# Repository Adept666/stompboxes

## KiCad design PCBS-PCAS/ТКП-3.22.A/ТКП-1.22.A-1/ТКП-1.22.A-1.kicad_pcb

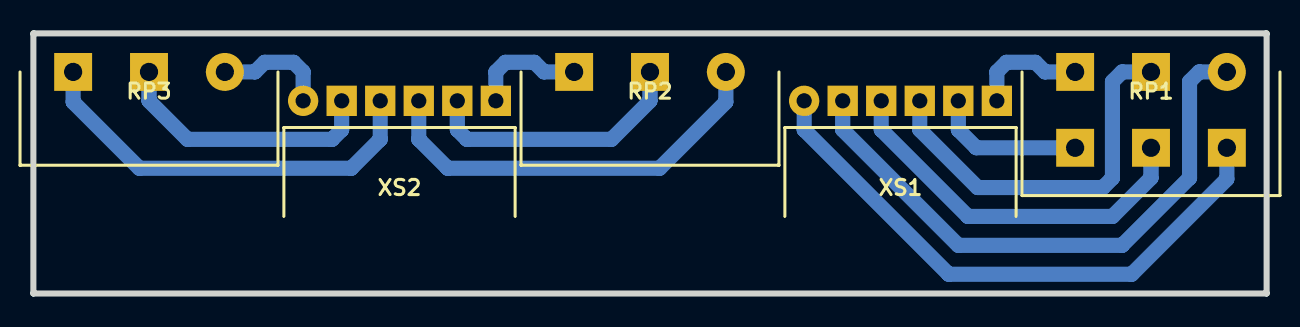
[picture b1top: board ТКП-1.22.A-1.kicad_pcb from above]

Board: 2 copper layers, 81.3 x 17.1 mm, 5 parts (0 on the bottom side), 12 nets.

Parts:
RP1: RP1: B100K; RP-PDB182-K-20-P
RP2: RP2: B10K; RP-PDB181-K-20-P
RP3: RP3: B10K; RP-PDB181-K-20-P
XS1, XS2: PBS-06R; CON-PBS-06R

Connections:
unnamed: RP1.1, XS1.2
unnamed: RP1.2, XS1.4
unnamed: RP1.3, XS1.6
unnamed: RP1.4, XS1.1
unnamed: RP1.5, XS1.3
unnamed: RP1.6, XS1.5
unnamed: RP2.1, XS2.4
unnamed: RP2.2, XS2.5
unnamed: RP2.3, XS2.6
unnamed: RP3.1, XS2.1
unnamed: RP3.2, XS2.2
unnamed: RP3.3, XS2.3

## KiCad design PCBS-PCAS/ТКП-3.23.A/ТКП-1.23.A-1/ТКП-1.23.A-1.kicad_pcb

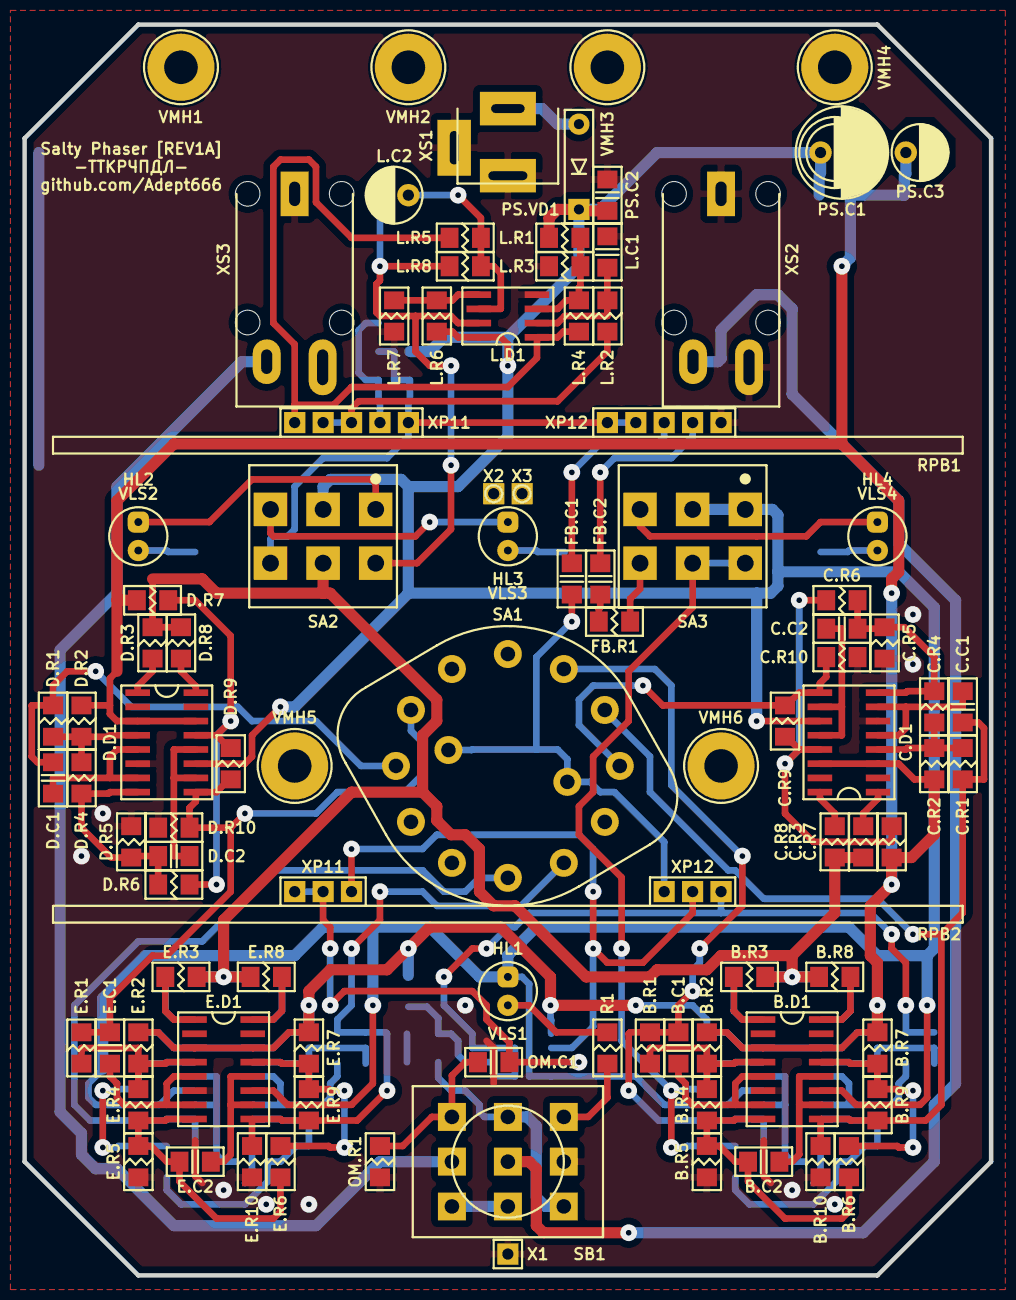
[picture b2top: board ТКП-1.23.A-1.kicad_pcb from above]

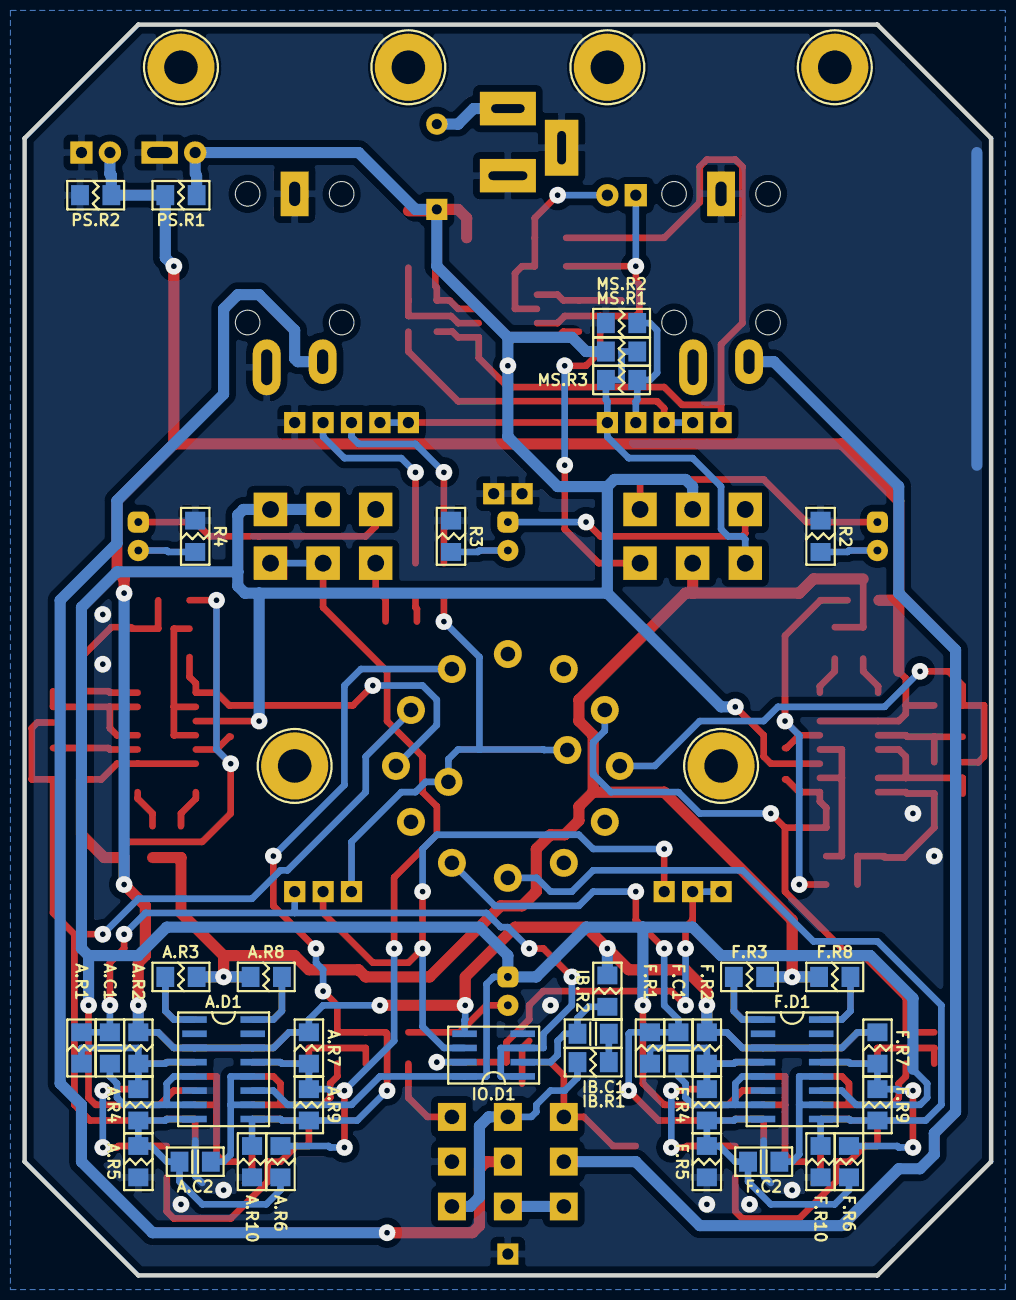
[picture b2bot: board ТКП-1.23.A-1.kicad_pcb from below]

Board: 2 copper layers, 86.4 x 111.8 mm, 160 parts (50 on the bottom side), 85 nets.

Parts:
*R1, *R2: 473; R-SM-0805
*R3: 2612; R-SM-0805
A.C1, A.C2: X; C-SM-1206
A.D1: X; P-SO-16
A.R1, A.R2, A.R3, A.R4, A.R5, A.R6, A.R7, A.R8, A.R9, A.R10: X; R-SM-1206
B.C1, B.C2: X; C-SM-1206
B.D1: X; P-SO-16
B.R1, B.R2, B.R3, B.R4, B.R5, B.R6, B.R7, B.R8, B.R9, B.R10: X; R-SM-1206
C.C1, C.C2: 332; C-SM-1206
C.D1: 13700; P-SO-16
C.R1, C.R4, C.R6, C.R9: 273; R-SM-1206
C.R2, C.R7: 182; R-SM-1206
C.R3, C.R5, C.R8, C.R10: 103; R-SM-1206
D.C1, D.C2: 332; C-SM-1206
D.D1: 13700; P-SO-16
D.R1, D.R4, D.R6, D.R9: 273; R-SM-1206
D.R2, D.R7: 182; R-SM-1206
D.R3, D.R5, D.R8, D.R10: 103; R-SM-1206
E.C1, E.C2: X; C-SM-1206
E.D1: X; P-SO-16
E.R1, E.R2, E.R3, E.R4, E.R5, E.R6, E.R7, E.R8, E.R9, E.R10: X; R-SM-1206
F.C1, F.C2: X; C-SM-1206
F.D1: X; P-SO-16
F.R1, F.R2, F.R3, F.R4, F.R5, F.R6, F.R7, F.R8, F.R9, F.R10: X; R-SM-1206
FB.C1, FB.C2: X; C-SM-1206
FB.R1: X; R-SM-1206
HL1: FYL-5013UWC; LED-ROUND-05.0-UNI-SH-SPACER-PNL-5.3
HL2, HL3, HL4: X; LED-ROUND-05.0-UNI-SH-SPACER-PNL-5.3
IB.C1: 472; C-SM-1206
IB.R1: 103; R-SM-1206
IB.R2: 105; R-SM-1206
IO.D1: 4558; P-SO-08
L.C1: 474; C-SM-1206
L.C2: 475; CP-RADIAL-D05.0-P02.0-CLS
L.D1: 4558; P-SO-08
L.R1, L.R3, L.R4: 364; R-SM-1206
L.R2: 154; R-SM-1206
L.R5, L.R6, L.R8: 103; R-SM-1206
L.R7: 622; R-SM-1206
MS.R1: 331; R-SM-1206
MS.R2: 680; R-SM-1206
MS.R3: 470; R-SM-1206
OM.C1: 473; C-SM-1206
OM.R1: X; R-SM-1206
PS.C1: 107; CP-RADIAL-D05.0-P02.0-CLS-OR-D06.3-P02.5-CLS-OR-D08.0-P03.5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
PS.C2: 104; C-SM-1206
PS.C3: 106; CP-RADIAL-D05.0-P02.0-CLS
PS.R1, PS.R2: 103; R-SM-1206
PS.VD1: 5817; P-DO-41
R1: 103; R-SM-1206
R2, R3, R4: X; R-SM-1206
RPB1: B500K-A1K-B100K; RPB-1590BB-18-3x17-1.5-PNL-7.4-2.8
RPB2: X; RPB-1590BB-18-2x17-1.5-PNL-7.4-2.8
SA1: X; SW-RBS-1-2P6W-VP-PNL-9.5
SA2: MTS-202-A2; SW-MTS-202-A2-3.0-PNL-6.0
SA3: X; SW-MTS-202-A2-3.0-PNL-6.0
SB1: PBS-24-302SP; SW-PBS-24-302SP-2.5-PNL-13.0
VE1: 1590BB; 1590BB_B1
VE2: ТКП-6.1.4.A1.A1.2-1.A1; ТКП-6.1.4.A1.A1
VJ1.1, VJ1.2, VJ3.1, VJ3.2, VJ3.3, VJ3.4: BOTTOM; VJ
VJ2.1, VJ2.2, VJ6.1, VJ6.2, VJ7.1, VJ7.2, VJ8.1, VJ8.2: TOP; VJ
VLS1: BR-12.7; VLS-BR
VLS2, VLS3, VLS4: X; VLS-BR
VMH1, VMH2, VMH3, VMH4, VMH5, VMH6: DI5M3x18; VMH-STA-DA5-PNL-3.0
VTC1, VTC2, VTC3: BOTTOM; VTC
VTC4: TOP; VTC
X1, X2: COM; CON-PAD-S-1.0-1.9
X3: X; CON-PAD-S-1.0-1.9
XS1: DC-005; CON-DC-005
XS2, XS3: ST-008S-05; CON-ST-008X-04-OR-ST-008X-05

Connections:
/DRY: A.C1.1, A.R1.1, IO.D1.1, IO.D1.3, RPB2.31, VJ1.1.1, VJ3.1.1, VJ3.4.1, VTC1.1, VTC3.1
/FB: A.D1.13, A.R6.2, A.R7.1, A.R9.1, SA3.COM2, SA3.NC2
/FB-ON: FB.R1.2, SA3.NO2
/IN-CIR: IB.R1.1, SB1.NC3, SB1.NO2
/IN-CON: SB1.COM2, XS2.T
/LED: R1.1, SB1.NO3
/LED-FB: HL4.A, SA3.NO1
/LED-MS: HL3.A, SA2.NO1
/LED-SPEED: HL2.A, SA2.NC1
/LFO: A.R3.1, A.R8.1, B.R3.1, B.R8.1, C.R3.1, C.R8.1, D.R3.1, D.R8.1, E.R3.1, E.R8.1, F.R3.1, F.R8.1, SA2.COM2
/LFO-AUTO: L.C2.-, L.D1.7, L.R8.2, SA2.NC2
/LFO-MANUAL: MS.R1.1, MS.R3.2, RPB1.22, RPB1.23, SA2.NO2
/OUT2: A.D1.9, A.R9.2, A.R10.1, B.C1.1, B.R1.1, SA1.1-1
/OUT4: B.D1.9, B.R9.2, B.R10.1, C.C1.1, C.R1.1, SA1.1-2, VJ3.3.1
/OUT6: C.D1.9, C.R9.2, C.R10.1, D.C1.1, D.R1.1, SA1.1-3, SA1.2-3, VJ6.1.1, VJ6.2.1
/OUT8: D.D1.9, D.R9.2, D.R10.1, E.C1.1, E.R1.1, SA1.2-4, VJ2.2.1
/OUT10: E.D1.9, E.R9.2, E.R10.1, F.C1.1, F.R1.1, SA1.1-5
/OUT12: F.D1.9, F.R9.2, F.R10.1, SA1.1-6
/OUT-CIR: OM.C1.2, OM.R1.2, SB1.NO1, VJ7.2.1, VJ8.2.1, VTC4.1
/OUT-CON: SB1.COM1, XS3.T
/WET: FB.C1.1, RPB2.33, SA1.COM1, SA1.COM2, VJ2.1.1
COM: A.D1.6, A.R5.2, A.R10.2, B.D1.6, B.R5.2, B.R10.2, C.D1.6, C.R5.2, C.R10.2, D.D1.6, D.R5.2, D.R10.2, E.D1.6, E.R5.2, E.R10.2, F.D1.6, F.R5.2, F.R10.2, IO.D1.4, L.C1.1, L.D1.4, L.R3.1, L.R7.1, MS.R2.1, OM.R1.1, PS.C1.-, PS.C2.2, PS.C3.-, PS.R2.1, R2.1, R3.1, R4.1, RPB1.31, SB1.COM3, VMH1.0, VMH2.0, VMH3.0, VMH4.0, X1.1, X2.1, X3.1, XS1.C, XS1.SN, XS2.R/TN, XS2.S, XS3.S
unnamed: A.C1.2, A.D1.5, A.D1.7
unnamed: A.C2.1, A.D1.8, A.R4.2, A.R5.1, A.R6.1
unnamed: A.C2.2, A.D1.10, A.D1.12
unnamed: A.D1.1, A.R3.2
unnamed: A.D1.4, A.R1.2, A.R2.1, A.R4.1
unnamed: A.D1.16, A.R8.2
unnamed: B.C1.2, B.D1.5, B.D1.7
unnamed: B.C2.1, B.D1.8, B.R4.2, B.R5.1, B.R6.1
unnamed: B.C2.2, B.D1.10, B.D1.12
unnamed: B.D1.1, B.R3.2
unnamed: B.D1.4, B.R1.2, B.R2.1, B.R4.1
unnamed: B.D1.13, B.R6.2, B.R7.1, B.R9.1
unnamed: B.D1.16, B.R8.2
unnamed: C.C1.2, C.D1.5, C.D1.7
unnamed: C.C2.1, C.D1.8, C.R4.2, C.R5.1, C.R6.1
unnamed: C.C2.2, C.D1.10, C.D1.12
unnamed: C.D1.1, C.R3.2
unnamed: C.D1.4, C.R1.2, C.R2.1, C.R4.1
unnamed: C.D1.13, C.R6.2, C.R7.1, C.R9.1
unnamed: C.D1.16, C.R8.2
unnamed: D.C1.2, D.D1.5, D.D1.7
unnamed: D.C2.1, D.D1.8, D.R4.2, D.R5.1, D.R6.1
unnamed: D.C2.2, D.D1.10, D.D1.12
unnamed: D.D1.1, D.R3.2
unnamed: D.D1.4, D.R1.2, D.R2.1, D.R4.1
unnamed: D.D1.13, D.R6.2, D.R7.1, D.R9.1
unnamed: D.D1.16, D.R8.2
unnamed: E.C1.2, E.D1.5, E.D1.7
unnamed: E.C2.1, E.D1.8, E.R4.2, E.R5.1, E.R6.1
unnamed: E.C2.2, E.D1.10, E.D1.12
unnamed: E.D1.1, E.R3.2
unnamed: E.D1.4, E.R1.2, E.R2.1, E.R4.1
unnamed: E.D1.13, E.R6.2, E.R7.1, E.R9.1
unnamed: E.D1.16, E.R8.2
unnamed: F.C1.2, F.D1.5, F.D1.7
unnamed: F.C2.1, F.D1.8, F.R4.2, F.R5.1, F.R6.1
unnamed: F.C2.2, F.D1.10, F.D1.12
unnamed: F.D1.1, F.R3.2
unnamed: F.D1.4, F.R1.2, F.R2.1, F.R4.1
unnamed: F.D1.13, F.R6.2, F.R7.1, F.R9.1
unnamed: F.D1.16, F.R8.2
unnamed: FB.C1.2, RPB1.33, VJ7.1.1
unnamed: FB.C2.1, RPB1.32, VJ8.1.1
unnamed: FB.C2.2, FB.R1.1
unnamed: HL1.C, R1.2
unnamed: HL2.C, R2.2
unnamed: HL3.C, R3.2
unnamed: HL4.C, R4.2
unnamed: IB.C1.1, IB.R1.2
unnamed: IB.C1.2, IB.R2.2, IO.D1.2, VJ1.2.1, VJ3.2.1, VTC2.1
unnamed: IO.D1.6, RPB2.11, RPB2.32
unnamed: IO.D1.7, OM.C1.1, RPB2.12, RPB2.13
unnamed: L.C1.2, L.D1.2, L.R2.1
unnamed: L.C2.+, L.D1.6, L.R5.2, L.R8.1
unnamed: L.D1.1, L.R4.2, L.R5.1, RPB1.13
unnamed: L.D1.3, L.R1.2, L.R3.2, L.R4.1
unnamed: L.D1.5, L.R6.2, L.R7.2
unnamed: L.R2.2, RPB1.11, RPB1.12
unnamed: MS.R2.2, MS.R3.1, RPB1.21
unnamed: PS.VD1.A, XS1.S
unnamed: SB1.NC1, SB1.NC2
V: A.D1.11, B.D1.11, C.D1.11, D.D1.11, E.D1.11, F.D1.11, HL1.A, IO.D1.8, L.D1.8, L.R1.1, L.R6.1, MS.R1.2, PS.C1.+, PS.C2.1, PS.R1.2, PS.VD1.C, SA2.COM1, SA3.COM1, SA3.NC1
VREF: A.D1.3, A.D1.14, A.R2.2, A.R7.2, B.D1.3, B.D1.14, B.R2.2, B.R7.2, C.D1.3, C.D1.14, C.R2.2, C.R7.2, D.D1.3, D.D1.14, D.R2.2, D.R7.2, E.D1.3, E.D1.14, E.R2.2, E.R7.2, F.D1.3, F.D1.14, F.R2.2, F.R7.2, IB.R2.1, IO.D1.5, PS.C3.+, PS.R1.1, PS.R2.2

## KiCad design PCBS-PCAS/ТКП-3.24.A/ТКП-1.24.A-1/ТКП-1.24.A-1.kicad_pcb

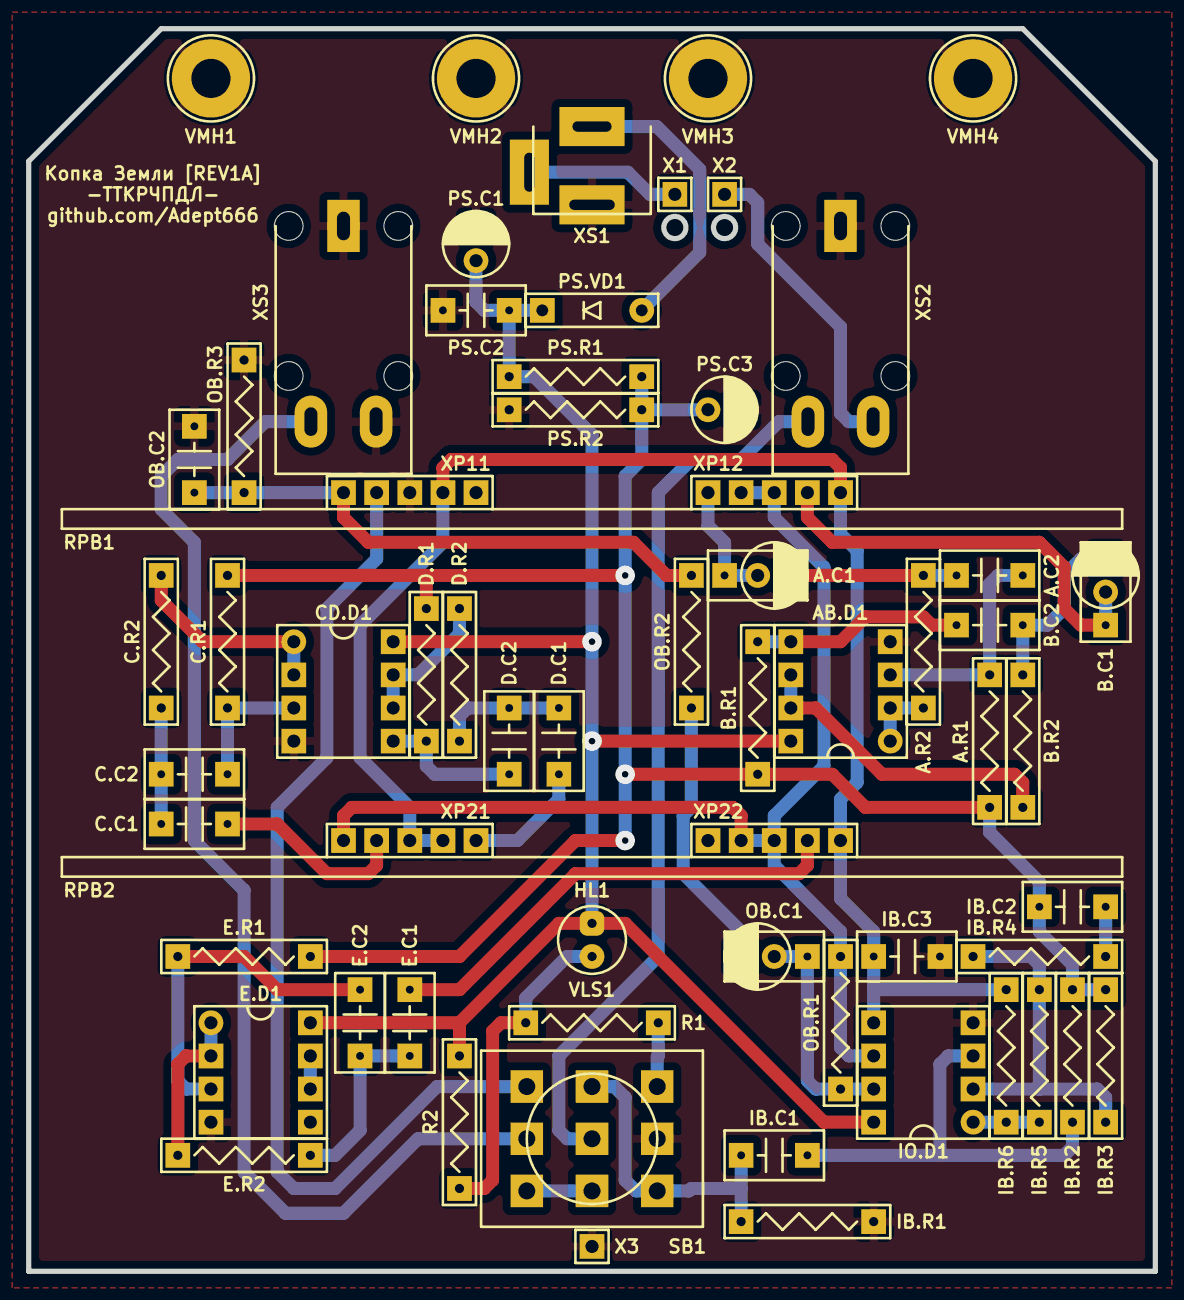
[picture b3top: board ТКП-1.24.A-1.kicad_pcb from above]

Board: 2 copper layers, 86.4 x 95.3 mm, 63 parts (0 on the bottom side), 43 nets.

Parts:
A.C1: 225; C-DISK-D04.2-T03.0-P05.08-d0.5-OR-CP-RADIAL-D05.0-P02.0-CLS
A.C2: 473; C-DISK-D04.2-T03.0-P05.08-d0.5
A.R1: 124; R-MFR-25
A.R2: 471; R-MFR-25
AB.D1: 4558; P-DIP-08
B.C1: 105; C-DISK-D04.2-T03.0-P05.08-d0.5-OR-CP-RADIAL-D05.0-P02.0-CLS
B.C2: 333; C-DISK-D04.2-T03.0-P05.08-d0.5
B.R1: 104; R-MFR-25
B.R2: 471; R-MFR-25
C.C1: 154; C-DISK-D04.2-T03.0-P05.08-d0.5
C.C2: 682; C-DISK-D04.2-T03.0-P05.08-d0.5
C.R1: 104; R-MFR-25
C.R2: 102; R-MFR-25
CD.D1: 4558; P-DIP-08
D.C1: 683; C-DISK-D04.2-T03.0-P05.08-d0.5
D.C2: 332; C-DISK-D04.2-T03.0-P05.08-d0.5
D.R1: 104; R-MFR-25
D.R2: 102; R-MFR-25
E.C1: 223; C-DISK-D04.2-T03.0-P05.08-d0.5
E.C2: 681; C-DISK-D04.2-T03.0-P05.08-d0.5
E.D1: 4558; P-DIP-08
E.R1: 104; R-MFR-25
E.R2: 102; R-MFR-25
GB1: PP3; B-PP3-HV
HL1: FYL-5013UWC; LED-ROUND-05.0-UNI-SH-SPACER-PNL-5.3
IB.C1, IB.C2: 103; C-DISK-D04.2-T03.0-P05.08-d0.5
IB.C3: 151; C-DISK-D04.2-T03.0-P05.08-d0.5
IB.R1: 225; R-MFR-25
IB.R2: 474; R-MFR-25
IB.R3, IB.R5, IB.R6: 103; R-MFR-25
IB.R4: 102; R-MFR-25
IO.D1: 4558; P-DIP-08
OB.C1: 105; C-DISK-D04.2-T03.0-P05.08-d0.5-OR-CP-RADIAL-D05.0-P02.0-CLS
OB.C2: 103; C-DISK-D04.2-T03.0-P05.08-d0.5
OB.R1, OB.R2, OB.R3: 103; R-MFR-25
PS.C1: 107; CP-RADIAL-D05.0-P02.0-CLS
PS.C2: 104; C-DISK-D04.2-T03.0-P05.08-d0.5
PS.C3: 476; CP-RADIAL-D05.0-P02.0-CLS
PS.R1, PS.R2: 473; R-MFR-25
PS.VD1: 5817; P-DO-41
R1: 103; R-MFR-25
R2: X; R-MFR-25
RPB1, RPB2: B50K-B50K-B50K; RPB-1590BB-18-3x17-1.5-PNL-7.4-2.8
SB1: PBS-24-302SP; SW-PBS-24-302SP-2.5-PNL-13.0
VE1: 1590BB; 1590BB_B1
VLS1: BR-12.7; VLS-BR
VMH1, VMH2, VMH3, VMH4: DI5M3x18; VMH-STA-DA5-PNL-3.0
X1: +; CON-PAD-S-1.0-1.9
X2: -; CON-PAD-S-1.0-1.9
X3: COM; CON-PAD-S-1.0-1.9
XS1: DC-005; CON-DC-005
XS2, XS3: PJ-309; CON-ST-008X-04

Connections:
/BOOST-RAIL: IO.D1.6, OB.R1.1, RPB1.23, RPB1.33, RPB2.13, RPB2.23, RPB2.33
/CUT-RAIL: IB.C3.1, IB.R6.2, IO.D1.5, RPB1.21, RPB1.31, RPB2.11, RPB2.21, RPB2.31
/IN-CIR: IB.C1.1, IB.R1.2, SB1.NC3, SB1.NO2
/IN-CON: SB1.COM2, XS2.T
/LED: R1.1, SB1.NO3
/OUT-CIR: RPB1.12, SB1.NO1
/OUT-CON: SB1.COM1, XS3.T
/PP3-NEG: X2.1, XS2.R
/PP3-POS: X1.1, XS1.SN
COM: AB.D1.4, CD.D1.4, E.D1.4, IB.C3.2, IB.R1.1, IO.D1.4, OB.C2.2, OB.R3.1, PS.C1.-, PS.C2.2, PS.C3.-, PS.R2.1, RPB1.11, SB1.COM3, VMH1.0, VMH2.0, VMH3.0, VMH4.0, X3.1, XS1.C, XS2.S, XS3.R, XS3.S
unnamed: A.C1.+, RPB1.22
unnamed: A.C1.-, A.C2.1, A.R2.1
unnamed: A.C2.2, A.R1.2, AB.D1.3
unnamed: A.R2.2, AB.D1.1, AB.D1.2
unnamed: AB.D1.5, B.C2.2, B.R1.2
unnamed: AB.D1.6, AB.D1.7, B.R2.2
unnamed: B.C1.+, RPB1.32
unnamed: B.C1.-, B.C2.1, B.R2.1
unnamed: C.C1.1, RPB2.12
unnamed: C.C1.2, C.C2.1, C.R2.1
unnamed: C.C2.2, C.R1.2, CD.D1.3
unnamed: C.R2.2, CD.D1.1, CD.D1.2
unnamed: CD.D1.5, D.C2.2, D.R1.2
unnamed: CD.D1.6, CD.D1.7, D.R2.2
unnamed: D.C1.1, RPB2.22
unnamed: D.C1.2, D.C2.1, D.R2.1
unnamed: E.C1.1, RPB2.32
unnamed: E.C1.2, E.C2.1, E.R2.1
unnamed: E.C2.2, E.D1.3, E.R1.2
unnamed: E.D1.1, E.D1.2, E.R2.2
unnamed: E.D1.6, E.D1.7
unnamed: HL1.C, R1.2, R2.1
unnamed: IB.C1.2, IB.R2.2, IO.D1.3
unnamed: IB.C2.2, IB.R4.1
unnamed: IB.R3.2, IB.R4.2, IB.R5.1, IO.D1.2
unnamed: IB.R5.2, IB.R6.1, IO.D1.1
unnamed: IO.D1.7, OB.C1.+, OB.R1.2
unnamed: OB.C1.-, OB.R2.1
unnamed: OB.C2.1, OB.R2.2, OB.R3.2, RPB1.13
unnamed: PS.VD1.A, XS1.S
unnamed: SB1.NC1, SB1.NC2
V: AB.D1.8, CD.D1.8, E.D1.8, HL1.A, IO.D1.8, PS.C1.+, PS.C2.1, PS.R1.2, PS.VD1.C, R2.2
VREF: A.R1.1, B.R1.1, C.R1.1, D.R1.1, E.R1.1, IB.C2.1, IB.R2.1, IB.R3.1, PS.C3.+, PS.R1.1, PS.R2.2

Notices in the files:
PCBS-PCAS/ТКП-3.22.A/ТКП-1.22.A-1/ТКП-1.22.A-1.kicad_pcb:
This project is licensed under GNU General Public License v3.0 or later
